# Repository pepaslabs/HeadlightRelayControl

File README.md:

# HeadlightRelayControl

A circuit board to control automotive headlight [relays](http://en.wikipedia.org/wiki/Relay).

## License

This board design is [Open-Source Hardware](http://www.oshwa.org/definition/).  It is licensed under the [MIT License](http://opensource.org/licenses/MIT).  It was designed by Jason Pepas.

# Board design v3

In this iteration of the board, the current-limiting resistors are replaced with constant-current sinks.

(*Board renders courtesy of [OSHPark](https://oshpark.com/shared_projects/iHltO6hv)*)

## Gerbers

[gerbers.zip](releases/v3/gerbers.zip)

## Schematic

[PDF](releases/v3/HeadlightRelayControl_schematic.pdf).

# Board design v2

This was the first iteration of the design (which had no mistakes!).

(*Board renders courtesy of [OSHPark](https://oshpark.com/shared_projects/l73fKEFv)*)

## Gerbers

[gerbers.zip](releases/v2/gerbers.zip)

## Schematic

[PDF](releases/v2/HeadlightRelayControl_schematic.pdf).

# Board design v1

(This release had an error and is deprecated.)

# Designing this circuit in LTSpice

Let's design this circuit using [LTSpice](http://www.linear.com/ltspice).

Start with the following basic circuit.  The [inductor](http://en.wikipedia.org/wiki/Inductor) L1 represents the coil inside of the relay.

## Specifying the relay coil parameters

Before we can simulate this circuit, we need to know some characteristics of the relay coil.  Specifically, we need to know the [inducatance](http://en.wikipedia.org/wiki/Inductance) and the [resistance](http://en.wikipedia.org/wiki/Electrical_resistance_and_conductance).

Here I've measured the inductance of a typical 12 Volt, 30 Amp automotive relay to be about 132 millihenries (using a cheap [LC100-A](http://www.ebay.com/sch/i.html?_nkw=LC100-A) meter from eBay):

Here, I've pulled up the [datasheet](http://www.te.com/commerce/DocumentDelivery/DDEController?Action=srchrtrv&DocNm=1432785-1&DocType=Customer+Drawing&DocLang=English) of a similar relay [listed on digikey.com](http://www.digikey.com/product-detail/en/1432785-1/PB680-ND/807757), where the resistance is listed as being 90 Ohms:

Right-click on L1 and fill in these parameters:

We want to simulate turning this relay on.  We can do this by creating a **PULSE** voltage source which will switch from 0V to 12V at 10 milliseconds.  Right-click on V1, then click advanced and fill in these parameters:

Simulate the relay for 100 milliseconds

Click on the green **I(L1)** label to create a cursor.  We can use the cursor to meausre the current, which is 133mA:

## Optimization: PICK and HOLD current

If you've ever operated an automotive relay at full voltage for a long period of time, you know they can get pretty hot.

It turns out that isn't necessary.  A relay only needs a short burst of full voltage (actually, current) to get the armature moving (this is called the **PICK** current).  Once switched, it requires only a fraction of that current (typically less than half of **PICK**) to keep the relay on (the **HOLD** current).

### Current-limiting resistor

We can add a 100 Ohm current-limiting resistor after the relay coil:

Now we have our **HOLD** current (63mA), but we've lost our **PICK** current.  This means our relay might not turn on reliably.

How can we have both a **PICK** and a **HOLD** current?  There are a few ways to implement this optimization.

### PWM the coil

We could [PWM](http://en.wikipedia.org/wiki/Pulse-width_modulation) the coil, perhaps using a purpose-built [IC](http://en.wikipedia.org/wiki/Integrated_circuit), such as the [DRV120](http://www.ti.com/lit/ds/symlink/drv120.pdf) made by [TI](http://www.ti.com/).

However, there even simpler, more hobbyist-friendly solutions...

### Bypass the current-limiting resistor

The technique I decided to use was to bypass the current-limiting resistor with a capacitor.

I came across this trick in a [blog post](http://jumperone.com/2011/10/using-relays/) by [Phil Levchenko](http://jumperone.com/about/).  Be sure to also check out his [YouTube channel](https://www.youtube.com/user/JumperOneTV).

First we will try a 10uF capacitor.  We will esitmate its [ESR](http://en.wikipedia.org/wiki/Equivalent_series_resistance) to be 1 Ohm.

Also, shorten the simulation window to just 50 milliseconds:

It worked!  We have both a **PICK** and a **HOLD** current.

However, our **PICK** current is small and not very long in duration, so a 10uF capacitor might not be enough to give us reliable relay operation.

Based on the [datasheet](http://www.te.com/commerce/DocumentDelivery/DDEController?Action=srchrtrv&DocNm=1432785-1&DocType=Customer+Drawing&DocLang=English) mentioned above, we should shoot for a **PICK** current window of around 8 milliseconds in duration, and we want it to be much closer to 133mA.

Next we'll try a 100uF capacitor.  Estimate the ESR to be 100 milliohms.

That's a lot closer to what we want.  Use a cursor to get a more exact idea of what our 8ms **PICK** window looks like.

Just to be thorough, we should also try a larger capacitor.  Try a 220uF (with 100mOhm ESR):

It looks like either 100uF or 200uF would work well.

When designing a circuit, you'll often find yourself in these "[Goldilocks](http://en.wikipedia.org/wiki/The_Story_of_the_Three_Bears)" scenarios, trying to find the value that's "just right".  Its a good idea to get better at this, so that you can iterate on a design faster.

The quick-n-dirty way to do this is to triplicate your circuit and simulate all three at once.

Eventually though, you'll want to learn how to [step the parameters of your simulations](http://www.linear.com/solutions/1089).

## Freewheeling diode

What happens when we switch the relay off?

Anytime you interrupt current flowing through an inductor, it creates a (negative) voltage spike, a.k.a an [inductive "kickback"](http://www.coilgun.info/theoryinductors/inductivekickback.htm) as the magnetic field in the inductor collapses.  This spike can can reach dozens, hundreds, or even thousands of Volts, which can damage other components in your circuit.

### Simulating inductive kickback

Does our circuit suffer from inductive kickback?  Let's ask LTSpice!

In order to simulate that, we need to use a switch, which is slightly complicated in LTSpice.

#### Wait, why can't we just turn the PULSE source off at, say, 40 milliseconds?

That would set the **PULSE** source to 0 Volts.  It turns out that's not the same thing as turning the circuit off (see also [Three-state logic](http://en.wikipedia.org/wiki/Three-state_logic)).

When we set a voltage source to 0 Volts, it **actively drives** the circuit to 0 Volts.  That's not the same thing as just disconnecting the voltage source.  That's more like replacing the voltage source with a short-circuit (to ground).

#### Using a switch in LTSpice

Grab [switch.mod](https://github.com/pepaslabs/LTSpice-parts/tree/master/parts/switch) and follow [my tutorial](https://github.com/pepaslabs/LTSpice-parts/wiki/switch) on how to incorporate it into a circuit.

Modify your circuit so that the switch is connected to the inductor:

Reconfigure the **PULSE** source to have a **Von** of 1 Volt and a **Ton** of 50 milliseconds:

Widen the simulation window to 100 milliseconds:

Run the simulation and probe the voltage between the switch and the inductor.

Houston, we have a problem (inductive kickback!):

(Note that with real-world components, you won't actually reach -600,000 Volts.  That only happens with idealized components in a simulator.).

Measuring the current through L1 gives you a better idea of what is going on here.  We are trying to instantaneously stop the current through the inductor, which causes the negative spike.

### So how do we get rid of the inductive kickback?

Inductive kickback is typically mitigated by placing a [freewheeling diode](http://en.wikipedia.org/wiki/Flyback_diode) (also called a flyback diode or snubber diode) across the inductor.  The negative spike is dissipated through the diode, which "clamps" the spike to no more than the [forward voltage drop](https://learn.sparkfun.com/tutorials/diodes/real-diode-characteristics) across the diode (typically 0.65 Volts).

Place a diode across the inductor.  Right-click on the diode and make it a [1N4148](http://en.wikipedia.org/wiki/1N4148).

Did it fix our negative voltage spike?

Yup!

(Notice the funny blip where the decaying voltage suddenly jumps back up a bit.  Note also that it jumps up by exactly 1 forward diode drop, at exactly the point when current finishes decaying in the inductor.)

## Feature: When you turn on the high-beams, keep the low-beams on

This control board has a feature where the low beams stay on when the high-beams are engaged.  This was implemented using a [diode OR](http://en.wikipedia.org/wiki/Diode-or_circuit).

Before we can simulate this feature, we need to duplicate our relay control circuit (to simulate both low beam and high beam), and put in an incomplete diode OR circuit (which we will complete later).

### Setup low beam and high beam circuits

Make a copy of the relay coil control circuit:

Setup two switches:

Create the (incomplete) diode OR:

The complete circuit should look like this:

Reconfigure the **PULSE** sources so that low beams turn on at 10 milliseconds for a duration of 20 milliseconds, and high beams turn on at 20 milliseconds for a duration of 20 milliseconds.  This will set up the following events:
* at T=10ms, low beams will turn on
* at T=20ms, high beams will turn on
* at T=30ms, low beams will turn off
* at T=40ms, high beams will turn off

Now, add the missing piece.  Complete the diode OR with an additional 1N4148:

Run the simulation again.  If the diode OR works, you should see the high beams prevent the low beams from turning off.

Bingo!

### Investigating a glitch

However, notice that the **HOLD** current through the low beam relay coil dips a bit at the point in time where the low beams are being held on by the high beams (when LB_power shuts off).

In our particular case, this dip isn't large enough for us to worry about (such a small dip won't cause the relay to turn off).

But let's examine what causes this anyway.  Create two additional traces which monitor LB_control and HB_control:

Ah, now this makes sense.  When LB_power shuts off, the current which keeps the low beam relay on has to go through D4 and then through D5.  This means it suffers a second diode drop (another 0.65 Volts) before it reaches the low beam coil.  That's what accounts for the slight dip in coil current.

This also means that when the high beams are keeping the low beams on, the current for both relay coils has to go through D4.  This provides us a nice segue into considering the power dissipation...

## Power dissipation

### Diode power dissipation

Let's examine the power dissipation in D3, D4, and D5.  Run a simulation and ALT-click on the diodes to create power dissipation traces.

The result is a bit confusing, because there are infinitesimally breif moments where the current spikes up over 100 Amps, which throws off the scale of the plot.  (We can safely ignore these spikes, as our real-world components will have parasitic capacitance and inductance which will greatly tame these spikes.  What remains will be so brief that it will be safely absorbed by the thermal mass of the diode).

Use the zoom tool to bring the situation to light:

Now we have a better picture of what's going on.  The worst case will be seen by D4 when the current for both high and low beam relay coils is flowing through it, at which point it will be dissipating 120 milliWatts.

Can the 1N4148 handle this?  Better check the datasheet.

Pulling up the [datasheet](http://www.vishay.com/docs/81857/1n4148.pdf) of a typical 1N4148, we see it is rated handle a dissipation of 440 milliWatts when TL (the [temperature of its leads](http://www.st.com/web/en/resource/technical/document/application_note/CD00183570.pdf)) is 45C (e.g., when it is in a hot environment).

For components like resistors and diodes, its a good design rule of thumb to [stay under half of the max rated dissipation](http://www.play-hookey.com/dc_theory/resistors/components_resistors.html).  For a 1N4148, that's 220mW, so we shouldn't have a problem at 120mW.

### Resistor power dissipation

Let's examine the power dissipation one of the current limiting resistors, R1.  ALT-click R1 to plot the power dissipation.

At 500mW, we should specify a 1 Watt resistor.

However, we want to keep this as hobbyist-friendly as possible, and a hobbyist is much more likely to have 1/4 Watt resistors on hand.  A trick we can use is to "quad-up" the resistor: replace the single resistor with four resistors in a series-parallel configuration.  This keeps the overall resistance value the same, but quadruples the power rating.  Each 1/4 Watt resistor would dissipate 125mW, which just meets our half-max design rule.

# Prototype

Now that we're reasonably sure our design is sound, the next step is to make a prototype.

I prefer to use [Manhattan style](https://www.google.com/search?q=manhattan+style+prototyping) construction on [copper clad](http://www.ebay.com/sch/i.html?_nkw=copper+clad).

Note that I used [terminal blocks](http://www.taydaelectronics.com/connectors-sockets/terminal-blocks/pcb-mount.html) to hold the bypass capacitors, so that I could easy swap them out and try different values of capacitance.

# Verification

Now that we have a prototype, we can compare its behavior to our LTSpice simulation.

Here, I've used a Vcc of 12V, using 220uF bypass capacitors, and I'm probing the voltage across the relay coil.

Pretty close!

Here's how I set this up in LTSpice.  To measure the voltage across a component (in this case, across L1), you have to manually edit the expression of a trace.

Create traces for the top and bottom of the L1 indcutor.  This identifies the node names for us.

Now right-click the **V(lb_control)** label to edit its expression.

Edit the expression to give you the difference in voltage.

Viola!

However, the scale of the plot does not line up with the results on the oscillosope.  Right click the plot and choose "Manual limits".  My scope has 12 horizontal divisions, and I'm at 10ms per division, so the LTSpice plot should be 120ms wide.  My scope has 8 vertical divisions and I'm at 2V per division, with a -6V offset, so my LTSpice plot should range from -2V to 14V in order to match the scope.

# See also:

* http://electronics.stackexchange.com/questions/34561/what-are-some-ways-to-use-relays-more-efficiently

# Background: The need for this circuit

## Why did I make this circuit?

After upgrading the aging, dim headlights on my (1997 Dodge Ram) pickup truck with an HID headlight kit from eBay, I ran into a problem: the stock headlight switch couldn't handle the higher current load of the HID headlights.

The spade connector on the headlight switch got so hot that the plastic which holds it in place started to melt.  Some of the melted plastic interfered with the connection, and the connector was no longer being securely held in place.  The result was that you had to wiggle the switch to get the headlights to come, and you could occaisionally smell burning plastic.  Eventually, the connection stopped working entirely.

## Why did the stock headlight switch fail?  Its hard to beleive the HIDs drew THAT MUCH more current...

True, there's more to this story than a simple matter of higher current draw.

Stock halogen headlights are spec'ed at 55 Watts.  If we assume that spec is for 12 Volts (rather than the 14.2 Volts you'd find in a running car), that means each lamp is drawing 55 / 12 = roughly 4.6 Amps.

The HID ballasts I use claim a max current draw of 10 Amps (they don't always draw 10 Amps, but they can go that high).  That's potentially more than twice the current which the stock headlight switch and wiring were designed around.

### HID ballasts look like a constant-wattage load

However, this problem is compounded by the fact that the HID ballasts are basically a constant-current supply, which means they look like a constant-wattage load to your car's electrical system.  This means that if you try to feed the ballast a lower voltage, it will simply draw more current to make up for it.  That's why they stay the same brightness even if your voltage droops a bit.

Resistive loads (like a traditional halogen bulb) don't behave like this.  If you lower the voltage, they draw fewer amps (and get dimmer).  If I had put 100 watt halogen bulbs in my truck, that would be bad (because they would try to draw 100 / 12 = 8.3 Amps), but it wouldn't be as precarious as the situation created by the HID ballasts.  Here's why:

When we turn on the 100 Watt halogen bulbs, they would draw 8.3 Amps.  The headlight switch (particularly the spade connector) and the wiring would start to heat up because we are drawing more current than they were rated for.  As they heat up, and their resistance would increase, which would create a voltage drop.  So now your bulbs only see maybe 10 Volts.  This means they draw less current, which means the headlight switch and wiring could start to cool down a bit, and eventually the whole system would settle out at some equilibrium.  This is how linear, resistive loads work.

### Thermal runaway

HID ballasts don't work like that.  The ballasts say their max draw is 10 Amps, but let's assume their normal, 12 Volt draw is only 6 Amps (72 Watts).  What happens when we turn them on?  Initially, the headlight switch and wiring aren't hot, and their resistance is low, and the HID ballast sees pretty close to 12 Volts, and draws 6 Amps.  But even 6 Amps is more than what the stock switch and wiring was designed to handle, so they start heating up, increasing in resistance, and creating a Voltage drop.  The HID ballasts are now only seeing 10 volts, and they compensate by increasing their current draw to 7.2 Amps (still 72 Watts).  This increased current draw causes the switch and wiring to heat up even more, become more resistive, and create an even bigger drop.  The ballast now sees only 8 Volts, and responds by drawing 9 Amps (still 72 Watts).  And now the switch and wiring heat up even more, and so on, and so on...

This situation is referred to as "thermal runaway".  The process would keep going indefinitely, except that the HID ballasts are designed with a safety mechanism where they will refuse to draw more than 10 Amps.  But at that point, the headlight switch and wiring are already hot enough to start burning the plastic and damaging the switch.

### Solution: use relays!

The solution to all of this is to use relays, which are high-current switches which are operated by a small current.  Typical automotive relays are rated to handle 30 Amps (more than enough for our HID ballasts) and they are typically controlled by about 0.125 Amps (125 milliamps).  This looks like a tiny, tiny load to your headlight switch, which means it won't even get warm, let alone hot enough to self-destruct.

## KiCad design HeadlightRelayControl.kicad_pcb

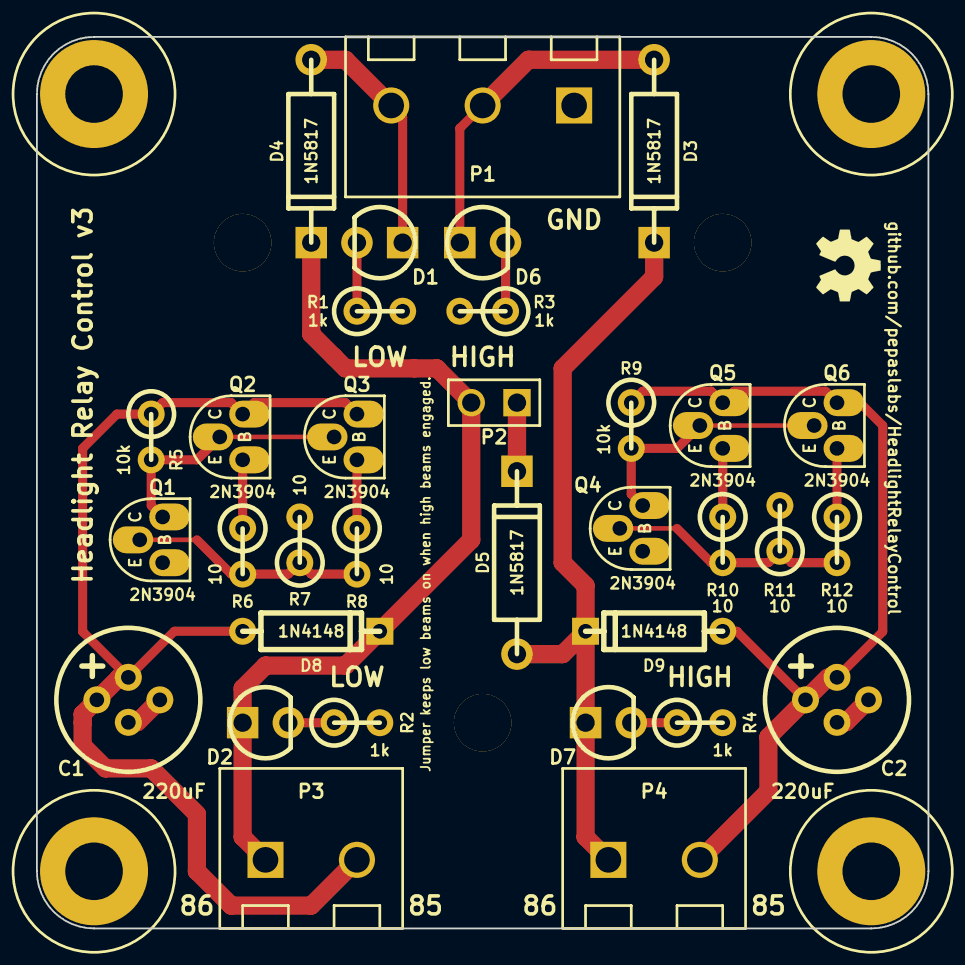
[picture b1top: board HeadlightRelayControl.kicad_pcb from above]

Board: 2 copper layers, 49.5 x 49.5 mm, 40 parts (0 on the bottom side), 20 nets.

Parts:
C1, C2: 220uF; MedCap
D1, D2, D6, D7: LED; LED_3MM_069A
D3, D4, D5: 1N5817; DIODE_1A_069A_PL
D8, D9: 1N4148; DIODE_3_059A
H1, H2, H3: HOLE; hole_M3_2
H7, H8, H9, H10: HOLE; hole_M3
P1: CONN_01X03; TERMINAL_BLOCK_3_5mm
P2: CONN_2; PIN_ARRAY_2X1
P3, P4: CONN_01X02; TERMINAL_BLOCK_2_5mm
Q1, Q2, Q3, Q4, Q5, Q6: 2N3904; TO-92_Q_EBC
R1, R2, R3, R4: 1k; R_AXIAL_0W25_V_059A
R5, R9: 10k; R_AXIAL_0W25_V_059A
R6, R7, R8, R10, R11, R12: 10; R_AXIAL_0W25_V_059A

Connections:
GND: C1.2, C2.2, P1.1, Q1.1, Q4.1, R1.2, R2.2, R3.2, R4.2, R7.2, R11.2
HighBeamControl: D3.2, D5.1, D7.1, D9.2, P4.1
HighBeamSignal: D3.1, D6.1, P1.2
LowBeamControl: D2.1, D4.2, D8.2, P2.2, P3.1
LowBeamSignal: D1.1, D4.1, P1.3
unnamed: Q1.3, Q2.2, Q3.2, R5.2
unnamed: C2.1, D9.1, P4.2, Q5.3, Q6.3, R9.1
unnamed: Q4.2, R10.2, R11.1, R12.2
unnamed: Q5.1, R10.1
unnamed: Q6.1, R12.1
unnamed: C1.1, D8.1, P3.2, Q2.3, Q3.3, R5.1
unnamed: Q3.1, R8.1
unnamed: Q2.1, R6.1
unnamed: Q1.2, R6.2, R7.1, R8.2
unnamed: Q4.3, Q5.2, Q6.2, R9.2
unnamed: D7.2, R4.1
unnamed: D1.2, R1.1
unnamed: D6.2, R3.1
unnamed: D5.2, P2.1
unnamed: D2.2, R2.1

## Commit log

2015-03-21 importing v1
2015-03-21 adding photos
2015-03-21 bugfix: a 1/4 watt resistor was seeing 500mW. broke it up into four 1/4w resistors. this is release v2.
2015-03-21 adding marked up photos
2015-03-21 adding ltspice screenshot
2015-03-21 adding screenshots
2015-03-21 adding screenshot.
2015-03-21 adding screenshot
2015-03-22 removing extraneous transistors. updated board labelling.
2015-03-22 Added corner mounting holes.
2015-03-22 creating PDF of schematic
2015-03-22 renaming schematic file (and copying to releases/v2)
2015-03-22 renaming schematic
2015-03-22 adding gerber renders (courtesy of OSHPark).
2015-03-22 adding photo
2015-03-22 adding scope shot
2015-03-22 adding comparison shot
2015-03-22 adding ltspice schematic
2015-03-24 adding v3 board design with constant current sinks on relay coils.
2015-03-24 adding board renders
2015-04-02 using update terminal block footprints.
2015-04-02 changing 1N4001 diodes to schottky 1N5817. updating diode footprints. adding substitution notes to schematic.
2015-04-02 updating board renders.
